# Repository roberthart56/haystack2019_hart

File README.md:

# haystack2019_hart
 Rob Hart's site for 2019 Haystack session 5 fablab

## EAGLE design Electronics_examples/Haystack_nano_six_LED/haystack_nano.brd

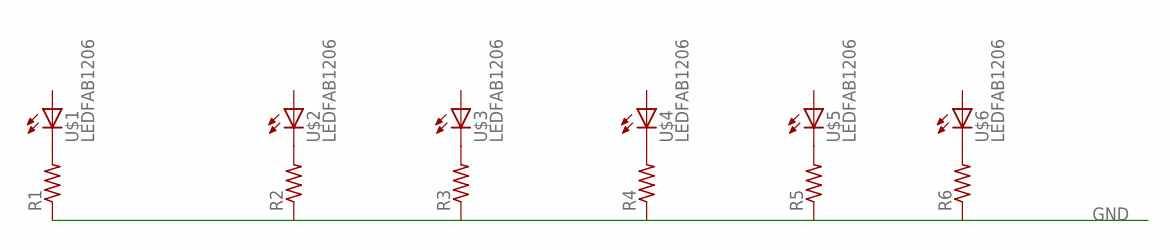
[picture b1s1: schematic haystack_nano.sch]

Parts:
R1, R2, R3, R4, R5, R6: RES-US1206; R1206
U$1, U$2, U$3, U$4, U$5, U$6: LEDFAB1206; LED1206FAB

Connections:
GND: R1.1, R2.1, R3.1, R4.1, R5.1, R6.1
unnamed: R1.2, U$1.2 (C)
unnamed: R2.2, U$2.2 (C)
unnamed: R3.2, U$3.2 (C)
unnamed: R5.2, U$5.2 (C)
unnamed: R6.2, U$6.2 (C)
unnamed: R4.2, U$4.2 (C)

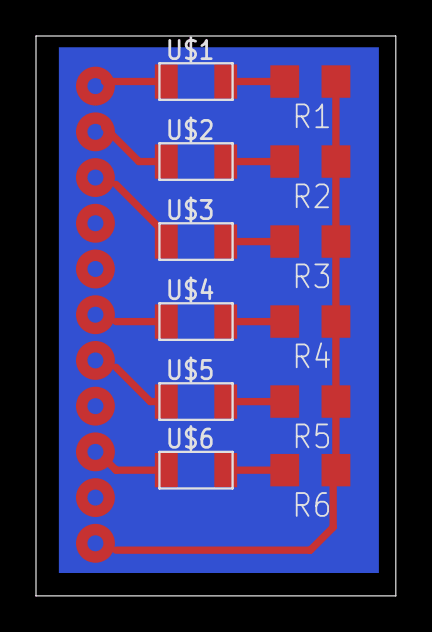
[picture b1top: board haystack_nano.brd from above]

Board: 2 copper layers, 20.0 x 31.1 mm, 12 parts (0 on the bottom side), 7 nets.

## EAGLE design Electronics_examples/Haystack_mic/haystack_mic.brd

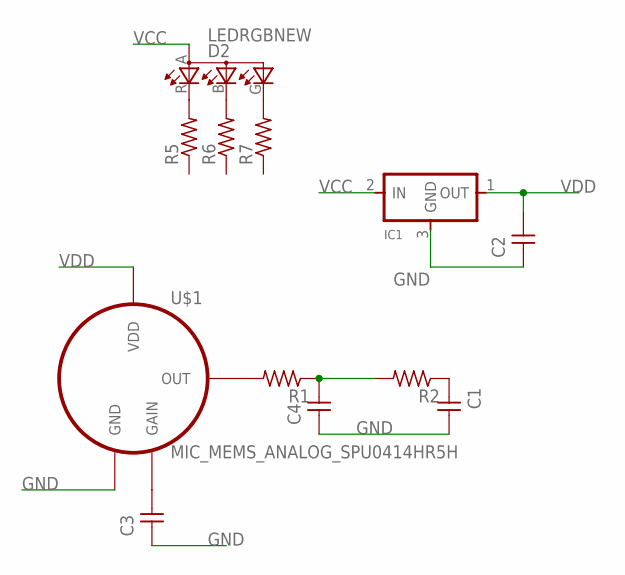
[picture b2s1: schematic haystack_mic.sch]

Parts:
C1, C2, C3, C4: CAP-UNPOLARIZED; C1206
D2: LEDRGBNEW; P-LCC-4
IC1: REGULATORSOT23; SOT23
R1, R2, R5, R6, R7: RES-US1206; R1206
U$1: MIC_MEMS_ANALOG_SPU0414HR5H

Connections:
GND: C1.2, C2.1, C3.1, C4.1, IC1.3 (GND), U$1.2 (GND)
unnamed: C1.1, R2.1
unnamed: D2.R (CRED), R5.2
unnamed: D2.B (CBLUE), R6.2
unnamed: D2.G (CGREEN), R7.2
unnamed: C3.2, U$1.3 (GAIN)
unnamed: R1.2, U$1.4 (OUT)
unnamed: C4.2, R1.1, R2.2
VCC: D2.A (A2), IC1.2 (IN)
VDD: C2.2, IC1.1 (OUT), U$1.1 (VDD)

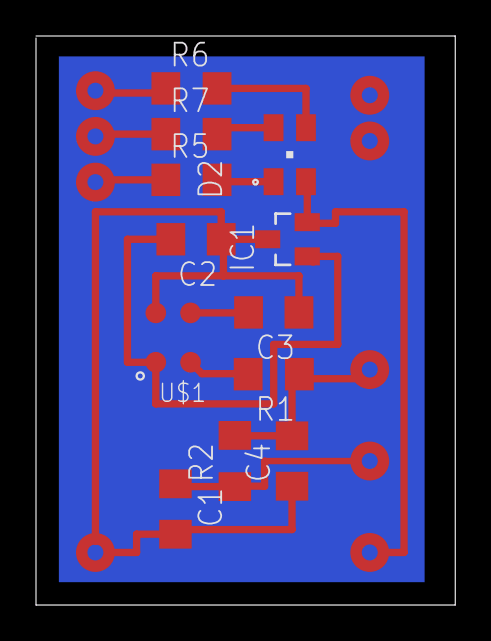
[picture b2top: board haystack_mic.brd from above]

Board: 2 copper layers, 23.3 x 31.6 mm, 12 parts (0 on the bottom side), 10 nets.

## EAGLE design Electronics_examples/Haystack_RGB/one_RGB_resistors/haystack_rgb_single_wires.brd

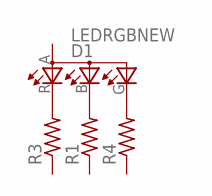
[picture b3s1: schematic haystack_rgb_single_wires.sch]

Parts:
D1: LEDRGBNEW; P-LCC-4
R1, R3, R4: RES-US1206; R1206

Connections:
unnamed: D1.B (CBLUE), R1.2
unnamed: D1.R (CRED), R3.2
unnamed: D1.G (CGREEN), R4.2

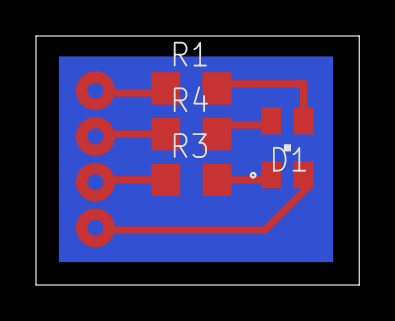
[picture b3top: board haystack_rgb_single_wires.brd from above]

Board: 2 copper layers, 18.0 x 13.8 mm, 4 parts (0 on the bottom side), 3 nets.

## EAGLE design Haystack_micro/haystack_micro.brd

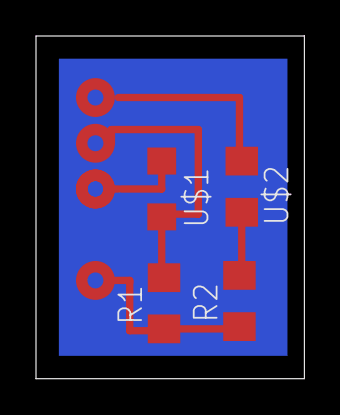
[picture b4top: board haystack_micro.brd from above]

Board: 2 copper layers, 14.9 x 19.0 mm, 4 parts (0 on the bottom side), 3 nets.

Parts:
R1, R2: R1206
U$1: PHOTOTRANSISTOR-NPN1206; OP1206
U$2: LED; LED1206

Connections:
A3: R1.2, U$1.EMITTER
GND: R1.1, R2.1
unnamed: R2.2, U$2.2

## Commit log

2019-09-01 add figures
2019-09-01 resize figs - too late, I know.
2019-09-01 copy figures
2019-09-03 added documentation links
2019-09-08 add links and move stuff
2019-09-08 various edits
2019-09-17 add movie
2019-09-17 edit index.html
2019-09-17 moved figs
2020-02-05 various
